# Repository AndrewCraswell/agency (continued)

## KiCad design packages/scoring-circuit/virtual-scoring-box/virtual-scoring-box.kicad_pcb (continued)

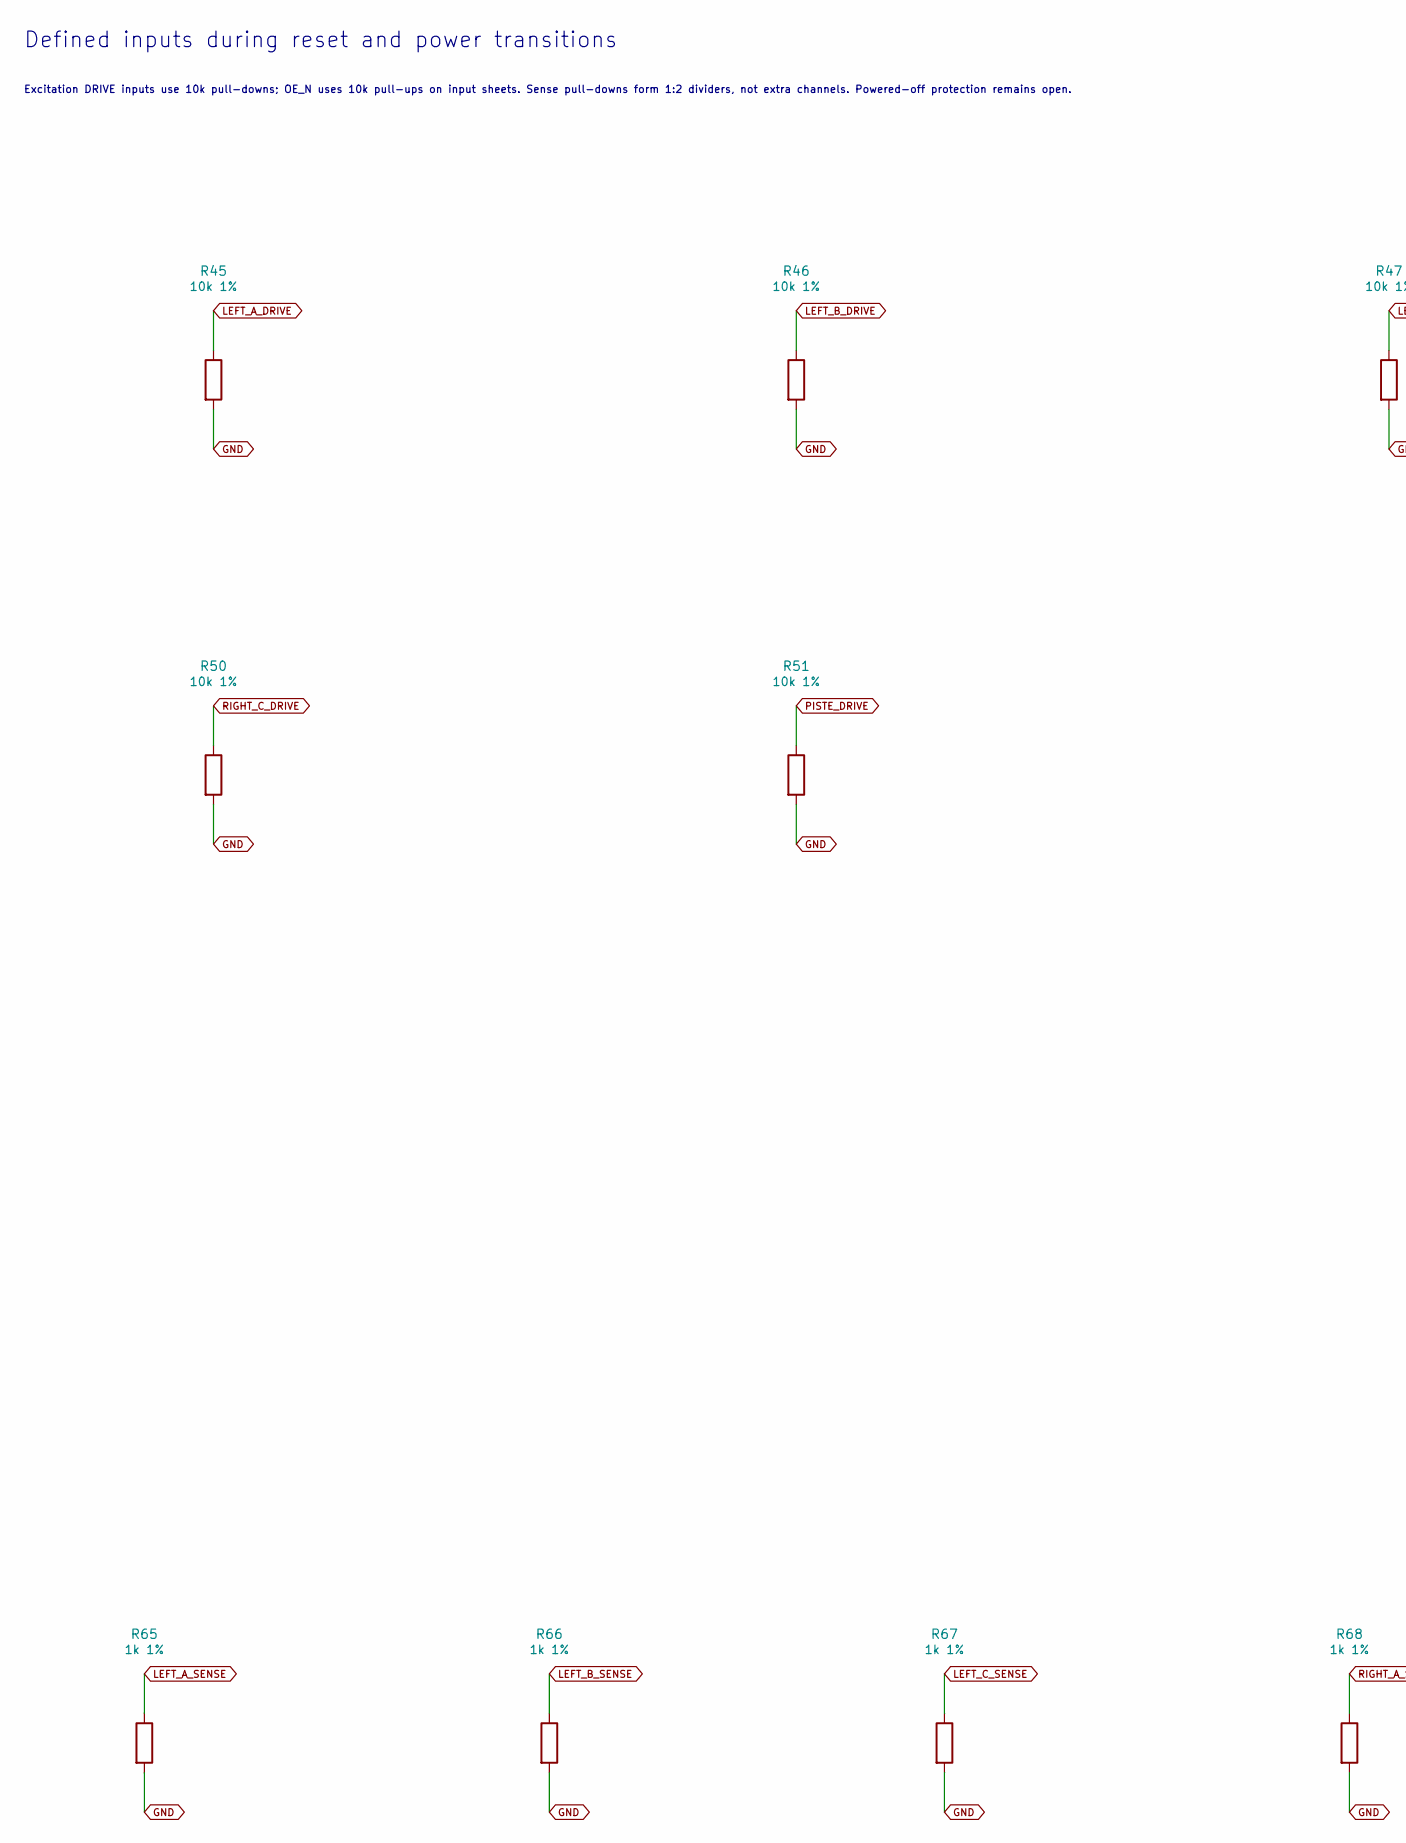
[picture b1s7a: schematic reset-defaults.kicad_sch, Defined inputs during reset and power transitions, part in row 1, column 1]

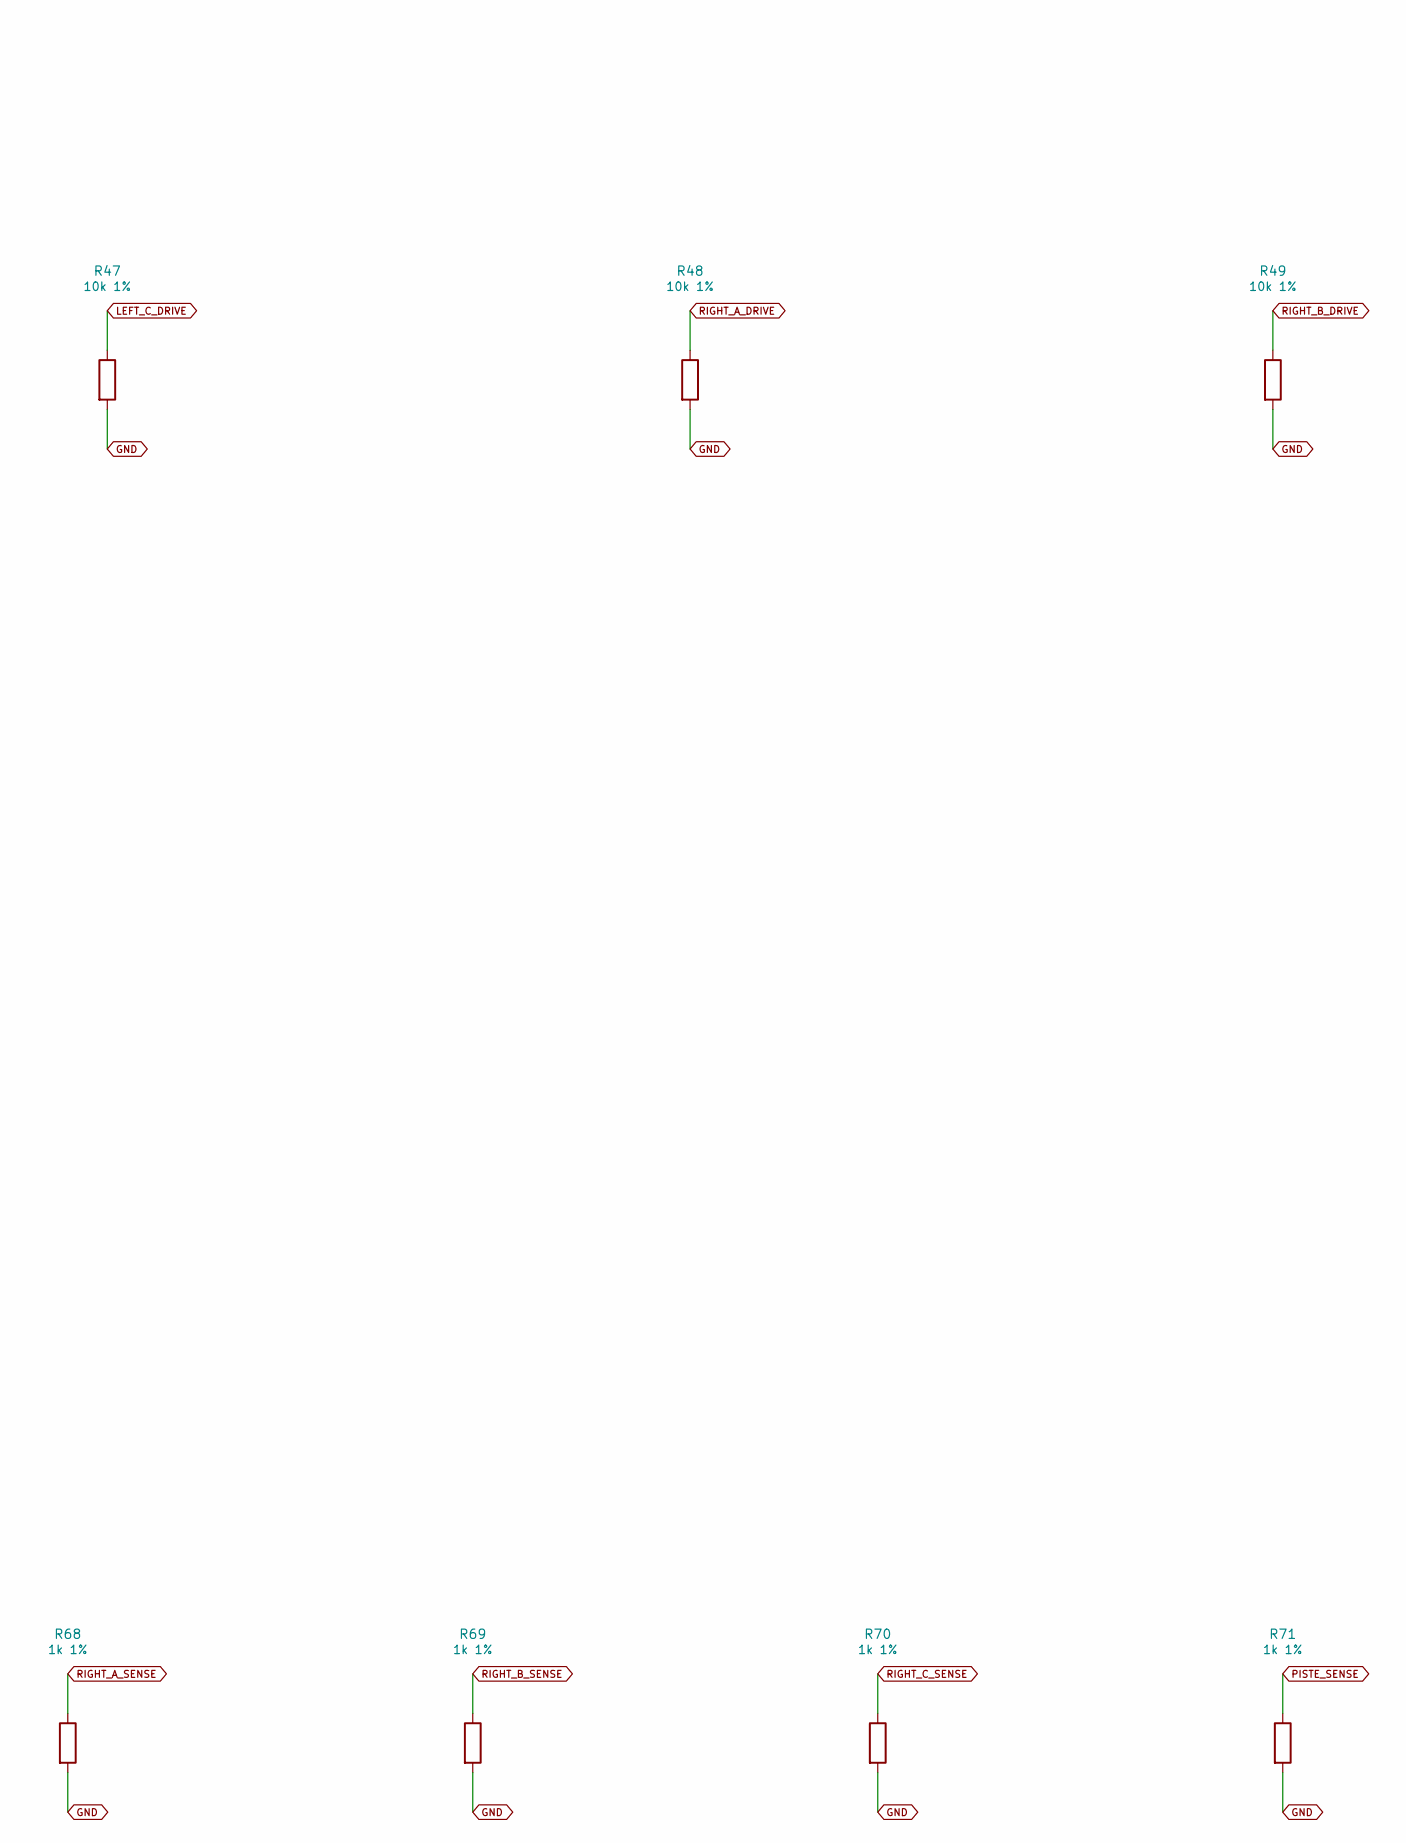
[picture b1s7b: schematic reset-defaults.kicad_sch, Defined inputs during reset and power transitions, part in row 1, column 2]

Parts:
R45, R46, R47, R48, R49, R50, R51: 10k 1%; R_0603_1608Metric; MPN RC0603FR-0710KL
R65, R66, R67, R68, R69, R70, R71: 1k 1%; R_0603_1608Metric; MPN RC0603FR-071KL

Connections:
GND: R45.2, R46.2, R47.2, R48.2, R49.2, R50.2, R51.2, R65.2, R66.2, R67.2, R68.2, R69.2, R70.2, R71.2; also elsewhere on the board
LEFT_A_DRIVE: R45.1; also elsewhere on the board
LEFT_A_SENSE: R65.1; also elsewhere on the board
LEFT_B_DRIVE: R46.1; also elsewhere on the board
LEFT_B_SENSE: R66.1; also elsewhere on the board
LEFT_C_DRIVE: R47.1; also elsewhere on the board
LEFT_C_SENSE: R67.1; also elsewhere on the board
PISTE_DRIVE: R51.1; also elsewhere on the board
PISTE_SENSE: R71.1; also elsewhere on the board
RIGHT_A_DRIVE: R48.1; also elsewhere on the board
RIGHT_A_SENSE: R68.1; also elsewhere on the board
RIGHT_B_DRIVE: R49.1; also elsewhere on the board
RIGHT_B_SENSE: R69.1; also elsewhere on the board
RIGHT_C_DRIVE: R50.1; also elsewhere on the board
RIGHT_C_SENSE: R70.1; also elsewhere on the board

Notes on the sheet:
Defined inputs during reset and power transitions
Excitation DRIVE inputs use 10k pull-downs; OE_N uses 10k pull-ups on input sheets. Sense pull-downs form 1:2 dividers, not extra channels. Powered-off protection remains open.

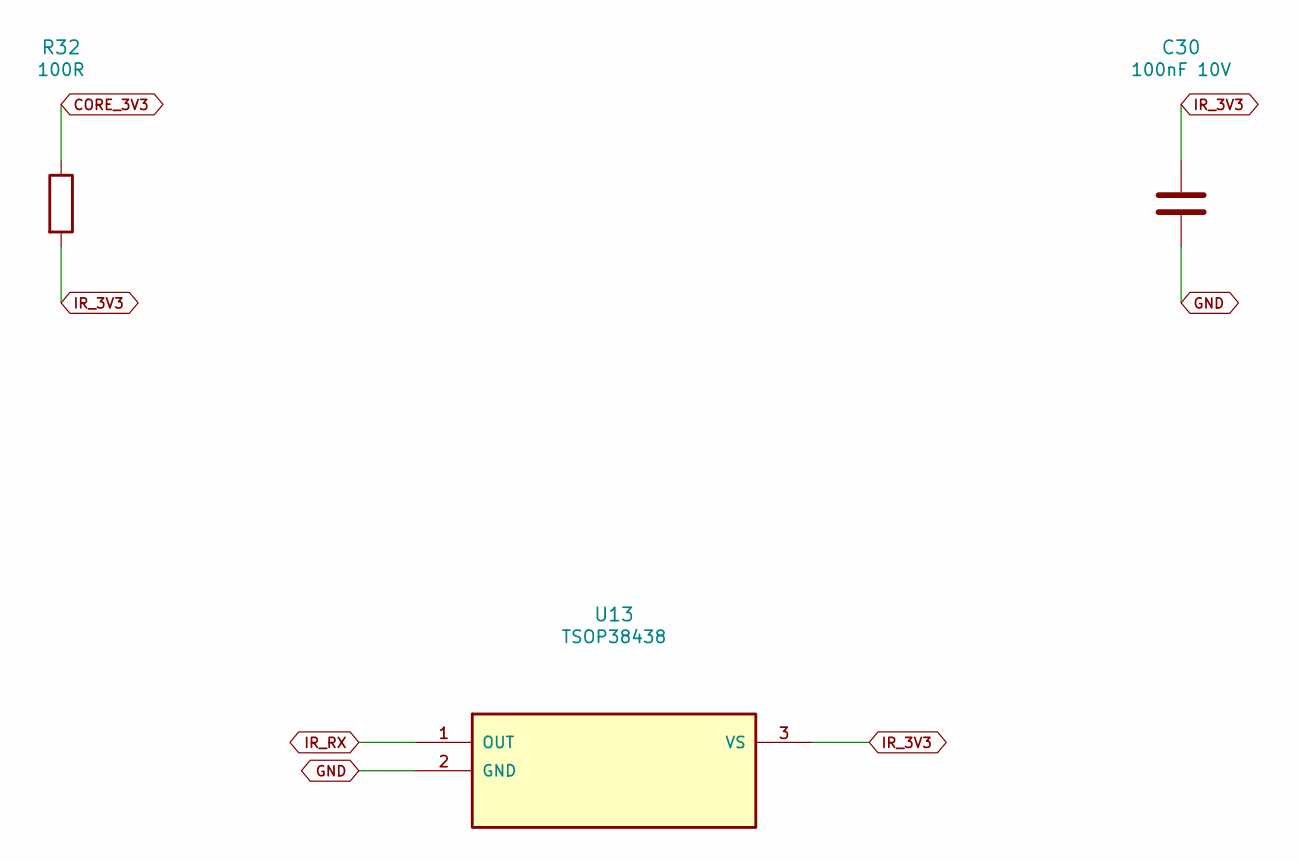
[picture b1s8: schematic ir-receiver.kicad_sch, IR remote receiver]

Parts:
C30: 100nF 10V; C_0603_1608Metric; MPN CC0603KRX7R9BB104
R32: 100R; R_0603_1608Metric; MPN RC0603FR-07100RL
U13: TSOP38438; MPN TSOP38438

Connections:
CORE_3V3: R32.1; also elsewhere on the board
GND: C30.2, U13.2 (GND); also elsewhere on the board
IR_3V3: C30.1, R32.2, U13.3 (VS)
IR_RX: U13.1 (OUT); also elsewhere on the board

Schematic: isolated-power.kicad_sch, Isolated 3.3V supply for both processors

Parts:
C41, C42, C43, C44, C45, C46: 10uF 16V X7R; C_1206_3216Metric; MPN C3216X7R1C106KT000N; JLCPCB C342827
C47: 100nF; C_0603_1608Metric; MPN CC0603KRX7R9BB104
D10, D11: SS14-E3/61T; D_SMA; MPN SS14-E3/61T
L1: 2.2uH; L_Coilcraft_XAL5030-XXX; MPN XAL5030-222MEC
R79: 100k; R_0603_1608Metric; MPN RC0603FR-07100KL
R80: 10k; R_0603_1608Metric; MPN RC0603FR-0710KL
T1: 750315371; MPN 750315371
U21: SN6505BDBVR; SOT-23-6; MPN SN6505BDBVR
U22: TPS62162DSGR; Texas_DSG0008A_WSON-8-1EP_2x2mm_P0.5mm_EP0.9x1.6mm_ThermalV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; MPN TPS62162DSGR

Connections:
CORE_3V3: C45.1, C46.1, L1.2, R80.1, U22.6 (VOS); also elsewhere on the board
CORE_BUCK_SW: L1.1, U22.7 (SW)
GND: C42.2, C43.2, C44.2, C45.2, C46.2, C47.2, R80.2, T1.5, U22.1 (PGND), U22.4 (AGND), U22.5 (FB), U22.9 (PAD); also elsewhere on the board
ISO_UNREG: C42.1, C43.1, C44.1, C47.1, D10.1 (K), D11.1 (K), U22.2 (VIN), U22.3 (EN)
SCORING_POWER_EN: R79.1, U21.5 (EN); also elsewhere on the board
STM_RESET_N: U22.8 (PG); also elsewhere on the board
USB_5V_PROTECTED: C41.1, T1.2, U21.2 (VCC); also elsewhere on the board
USB_GND: C41.2, R79.2, U21.4 (GND), U21.6 (CLK); also elsewhere on the board
XFMR_PRI_A: T1.3, U21.1 (D1)
XFMR_PRI_B: T1.1, U21.3 (D2)
XFMR_SEC_A: D10.2 (A), T1.6
XFMR_SEC_B: D11.2 (A), T1.4

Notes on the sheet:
Isolated supply: protected 5V -> push-pull transformer -> rectifier -> 3.3V / 1A buck
Design target: 0.8A combined 3.3V load, including ESP32 radio peaks, STM32 and acquisition circuits. C45/C46 provide 20uF nominal; 2.2uH / 20uF is within the TPS6216x recommended LC range. T1 is 1:1.1, with primary center tap pin 2 and isolated secondary center tap pin 5. USB_GND must never connect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

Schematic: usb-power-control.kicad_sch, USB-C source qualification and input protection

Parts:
C48, C51, C53, C55, C56, C57, C58: 100nF; C_0603_1608Metric; MPN CC0603KRX7R9BB104
C49, C50, C52: 1uF; C_0603_1608Metric; MPN CC0603KRX7R9BB105; JLCPCB C559769
C54: 10nF; C_0603_1608Metric; MPN CC0603KRX7R9BB103
J7: PRIMARY SWD PADS; Primary_SWD_Pads; MPN PCB contact pads
R81: 23.7k 0.1%; R_0603_1608Metric; MPN RT0603BRD0723K7L; JLCPCB C861245
R82, R84: 10k 0.1%; R_0603_1608Metric; MPN ERA3AEB103V; JLCPCB C190610
R83: 34.8k 0.1%; R_0603_1608Metric; MPN RT0603BRD0734K8L; JLCPCB C861338
R85: 2.74k; R_0603_1608Metric; MPN RC0603FR-072K74L
R86, R87: 4.7k; R_0603_1608Metric; MPN RC0603FR-074K7L
R88, R92: 47k; R_0603_1608Metric; MPN AF0603FR-0747KL; JLCPCB C144107
R89, R90, R91: 100k; R_0603_1608Metric; MPN RC0603FR-07100KL
R93, R94: 1k 1W; R_2512_6332Metric; MPN RC2512FK-071KL
R95: 10k; R_0603_1608Metric; MPN RC0603FR-0710KL
U23: STUSB4500QTR; MPN STUSB4500QTR
U24: STM32C011F6P6; TSSOP-20_4.4x6.5mm_P0.65mm; MPN STM32C011F6P6
U25: TPS259470ARPWR; TPS25947_RPW; MPN TPS259470ARPWR
U26: SN74LVC1G3208DBVR; SOT-23-6; MPN SN74LVC1G3208DBVR
U27: SN74LVC1T45DBVR; SOT-23-6; MPN SN74LVC1T45DBVR

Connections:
FUSE_FAULT_N: R92.2, U24.8 (PA1), U25.4 (FLT_N)
INPUT_DVDT: C54.1, U25.7 (DVDT)
INPUT_ILM: R85.1, U25.9 (ILM)
INPUT_OVLO: R83.2, R84.1, U25.2 (OVLO)
INPUT_UVLO: R81.2, R82.1, U25.1 (EN_UVLO)
PD_1V2: C49.1, U23.21 (VREG_1V2)
PD_2V7: C50.1, U23.23 (VREG_2V7)
PD_ALERT_N: R88.2, U23.19 (ALERT), U24.13 (PA6)
PD_DISCH: R93.2, U23.9 (DISCH)
PD_RESET: R89.1, U23.6 (RESET), U24.7 (PA0)
PD_SCL: R86.2, U23.7 (SCL), U24.20 (PB6)
PD_SDA: R87.2, U23.8 (SDA), U24.1 (PB7)
PD_VBUS_SENSE: R94.2, U23.18 (VBUS_VS_DISCH)
PRIMARY_RESET_N: C58.1, J7.5, R95.2, U24.6 (PF2)
PRIMARY_SWCLK: J7.4, U24.19 (PA14)
PRIMARY_SWDIO: J7.3, U24.18 (PA13)
SCORING_ENABLE_3V3: U26.4, U27.3 (A)
SCORING_POWER_EN: U27.4 (B); also elsewhere on the board
SOURCE_ALLOWED: R90.1, U24.11 (PA4), U26.6
USB_5V_PROTECTED: C57.1, U25.6 (OUT), U27.6 (VCCB); also elsewhere on the board
USB_AWAKE: U24.14 (PA7), U26.1; also elsewhere on the board
USB_CC1: U23.1 (CC1DB), U23.2 (CC1); also elsewhere on the board
USB_CC2: U23.4 (CC2), U23.5 (CC2DB); also elsewhere on the board
USB_GND: C48.2, C49.2, C50.2, C51.2, C52.2, C53.2, C54.2, C55.2, C56.2, C57.2, C58.2, J7.2, R82.2, R84.2, R85.2, R89.2, R90.2, R91.2, U23.10 (GND), U23.12 (ADDR0), U23.13 (ADDR1), U23.22 (VSYS), U23.25 (GND), U24.5 (VSS), U25.8 (GND), U26.2 (GND), U27.2 (GND); also elsewhere on the board
USB_HOST_3V3: C51.1, C52.1, C55.1, C56.1, J7.1, R86.1, R87.1, R88.1, R92.1, R95.1, U24.4 (VDD), U26.5 (VCC), U27.1 (VCCA), U27.5 (DIR); also elsewhere on the board
USB_SUSPEND_EXEMPT: R91.1, U24.12 (PA5), U26.3
USB_VBUS: C48.1, C53.1, R81.1, R83.1, R93.1, R94.1, U23.24 (VDD), U25.5 (IN); also elsewhere on the board

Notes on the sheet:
USB-C 5V input: source qualification, voltage/current protection, hardware suspend cutoff
U23 NVM: one 5V / 1.5A sink PDO; program and read back before shipment. No higher-voltage load mode. SOURCE_ALLOWED requires advertised Type-C >=1.5A OR a valid 5V PD contract >=1.5A; default OFF. USB_SUSPEND_EXEMPT requires current, fresh source evidence, not merely a requested RDO flag. U26: (USB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

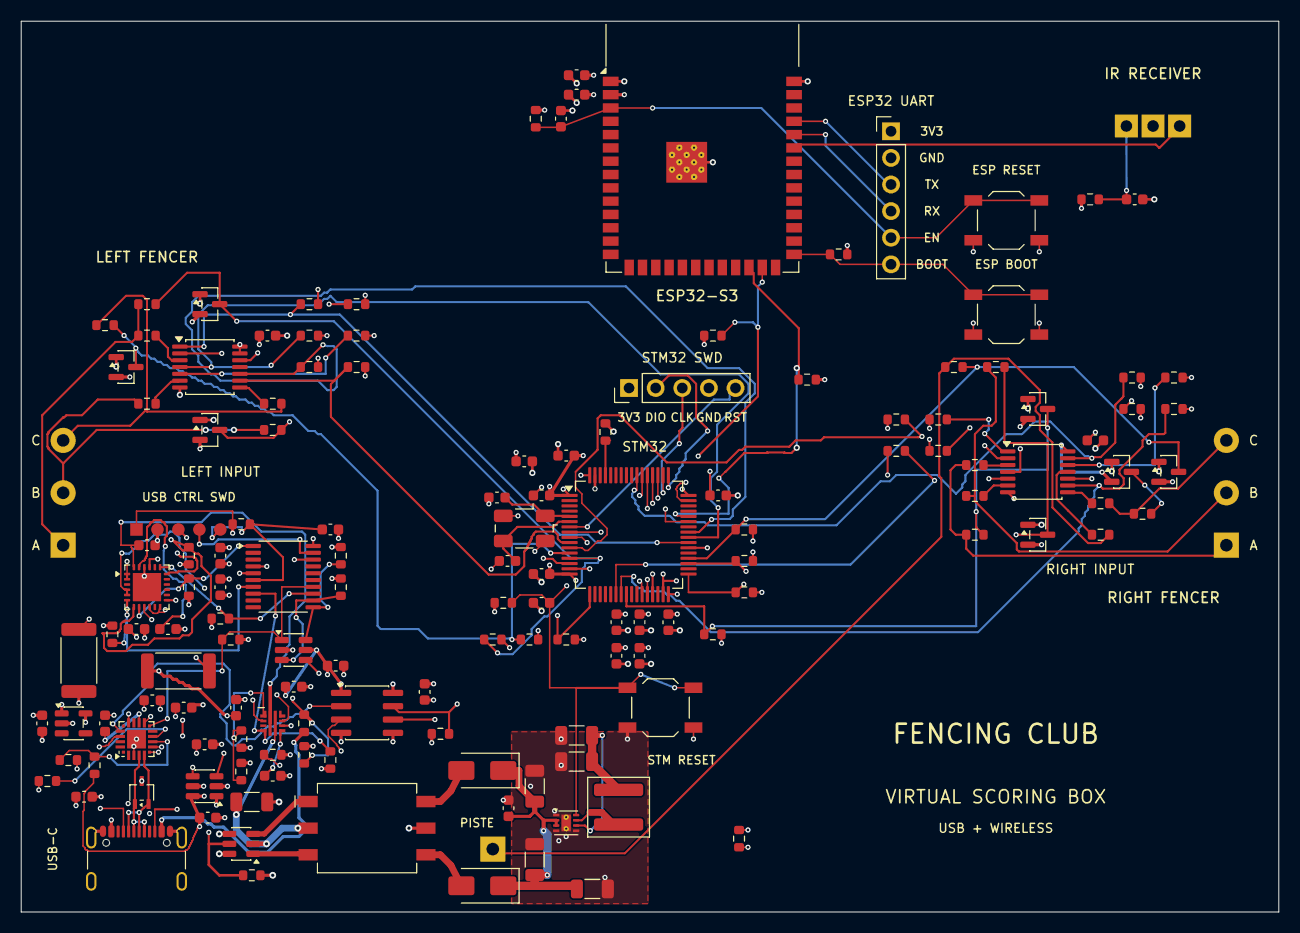
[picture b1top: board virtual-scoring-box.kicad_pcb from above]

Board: 4 copper layers, 120.0 x 85.0 mm, 146 parts (0 on the bottom side), 92 nets.

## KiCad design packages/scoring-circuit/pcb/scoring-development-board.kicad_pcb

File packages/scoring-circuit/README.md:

# Scoring prototype hardware

## Native KiCad designs

- **Active: [virtual scoring box](virtual-scoring-box/README.md).** STM32 scoring, ESP32 wireless/IR, and laptop or
  wall-powered USB-C. The 120 x 85mm board is routed and has a 142-part assembly export. Its README records the current
  JLCPCB draft, component shortages and programming handoff; it is not yet order-ready.
- **Frozen: [combined computer/standalone board](usb-scoring-platform/README.md).** The 165 x 100mm, 223-part design
  includes isolated USB, USB-C PD, Ethernet, IR, HUB75, audio and Favero outputs. Preserve it as a separate reference;
  do not overwrite it with either dedicated product. Its [design review](usb-scoring-platform/design-review.md) retains
  unresolved findings and component checks, not fabrication approval.
- **Active: [standalone HUB75 scoring box](standalone-scoring-box/README.md).** Separate native schematic and routed 165
  x 100mm board with 199 purchased parts. Retains STM32, ESP32, IR, fencer/piste connections, HUB75, Ethernet, Favero
  outputs, audio and power-only USB-C PD; removes the laptop interface and source-mode MCU. The power desk review, U5
  programming procedure and manufacturing exporter are supplied. Four mounting holes and the Ethernet footprint have
  been reviewed; a separate JLCPCB draft is saved. Its README records 34 unresolved sourcing/catalog references, plus
  impedance/programming and physical-test work. It is not order-ready. Firmware logic stays shared, with board-specific
  hardware adapters.

For each native design, use its own README and manufacturing exporter. Keep the latest supplier-upload package and
required programming handoff; older output checkpoints, build caches and scratch routing scripts are disposable. Keep
source, required component models and manufacturer references. Generated output is not a second source of truth.

## Earlier tscircuit carrier

The ESP32 DevKitC/WIZ850io carrier is preserved as the explicitly requested comparison design. Its
[architecture](docs/clean-sheet-board-architecture.md), source and models describe that carrier, not the native board.
Do not mix its BOM, pinout or generated fabrication files with the USB scoring platform.

The following commands operate on that earlier carrier only, not the native KiCad designs.

- `pnpm --filter @repo/scoring-circuit build` generates the circuit JSON, the locally bundled tscircuit RunFrame PCB,
  schematic, and 3D preview, plus the BOM and placement files in `dist/`.
- `pnpm --filter @repo/scoring-circuit pcb:route` regenerates the KiCad project, Gerbers, drill files, BOM, and
  placement files in `pcb/`.
- `pnpm --filter @repo/scoring-circuit test` runs the focused board tests.

The board source sets a red solder mask and white silkscreen for the preview. Gerbers define the mask and silkscreen
geometry, but the fabricator's order form or fabrication notes select the physical pigment; change `solderMaskColor` and
`silkscreenColor` in `src/index.circuit.tsx` when a different finish is chosen.

This is a prototype, not a production or FIE-certified board. Review the KiCad board and fabrication preview before
ordering, then validate the assembled hardware electrically before connecting it to fencing equipment.

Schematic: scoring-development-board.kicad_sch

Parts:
BZ_P0: CMI-9605-0580T
C_APP_REG_BOOT: 100nF
C_APP_REG_IN: 4.7uF
C_APP_REG_IN_HF: 100nF
C_APP_REG_OUT_A: 22uF
C_APP_REG_OUT_B: 22uF
C_APP_REG_OUT_C: 22uF
C_APP_REG_VCC: 1uF
C_DISPLAY_BYPASS: 100nF
C_DISPLAY_DVDT: 2.2nF
C_DISPLAY_IN: 22uF
C_DISPLAY_ITIMER: 2.2nF
C_DISPLAY_OUT: 22uF
C_ESP_3V3_BULK: 47uF
C_ESP_3V3_HF: 100nF
C_ESP_EN_DELAY: 1uF
C_HUB75_BUF_A_BYPASS, C_HUB75_BUF_B_BYPASS: 100nF
C_IR_VS: 100nF
C_NEG_FLY: 1uF
C_NEG_IN: 1uF
C_NEG_OUT: 1uF
C_PHASE_CONTROL_1, C_PHASE_CONTROL_2: 100nF
C_REF_IN: 1uF
C_REF_REG: 10uF
C_REF_REG_HF: 100nF
C_REF_SAR: 10uF
C_SAR: 1nF
C_SAR_AVDD: 1uF
C_SAR_DVDD: 1uF
C_SENSE_MUX: 100nF
C_SENSE_NEG_2, C_SENSE_NEG_3, C_SENSE_NEG_5, C_SENSE_NEG_6, C_SENSE_NEG_7: 100nF
C_SENSE_POS_2, C_SENSE_POS_3, C_SENSE_POS_5, C_SENSE_POS_6, C_SENSE_POS_7: 100nF
C_SINK_MUX: 100nF
C_SOURCE_MUX: 100nF
D_P0_GREEN: WP7113SGD
D_P0_RED: WP7113ID
D_P0_WHITE_LEFT, D_P0_WHITE_RIGHT: WP7113QWC/D
F_DISPLAY: 045106.3MRL
F_MAIN_5V: 0451003.NRL
F_P0_OUTPUTS: 1206L020YR
J_DISPLAY_POWER_PIGTAIL: (no value)
J_HUB75: TST-108-04-G-D-RA
J_PISTE_DIRECT: (no value)
J_POWER_INPUT: OSTVN02A150
J_PRIMARY_OUTPUTS: J_PRIMARY_OUTPUTS
J_USB_C: 10177070-00011LF
J_WEAPON_DIRECT: (no value)
L_APP_REGULATOR: XGL4030-222MEC
Q_DISPLAY_ENABLE: BSS138AKA
R_APP_REG_DISCHARGE: 1kΩ
R_DISPLAY_ENABLE_GATE: 10kΩ
R_DISPLAY_ENABLE_GATE_PD: 100kΩ
R_DISPLAY_ENABLE_PULLUP: 10kΩ
R_DISPLAY_ILM: 698Ω
R_DISPLAY_PG_LOWER: 49.9kΩ
R_DISPLAY_PG_PULLUP: 10kΩ
R_DISPLAY_PG_UPPER: 137kΩ
R_ESP_BOOT_PULLUP: 10kΩ
R_ESP_EN_PULLUP: 10kΩ
R_HUB75_A_PD, R_HUB75_B1_PD, R_HUB75_B2_PD, R_HUB75_B_PD, R_HUB75_CLK_PD, R_HUB75_C_PD, R_HUB75_D_PD, R_HUB75_G1_PD, R_HUB75_G2_PD, R_HUB75_LAT_PD, R_HUB75_OE_PULLUP, R_HUB75_PANEL_OE_PULLUP, R_HUB75_R1_PD, R_HUB75_R2_PD, R_HUB75_UNUSED_B_A6_PD, R_HUB75_UNUSED_B_A7_PD, R_HUB75_UNUSED_B_A8_PD: 10kΩ
R_IR_OUT: 100Ω
R_IR_PULLUP: 10kΩ
R_IR_VS: 100Ω
R_LINE_1, R_LINE_2, R_LINE_3, R_LINE_4, R_LINE_5, R_LINE_6, R_LINE_7: 22Ω
R_P0_BUZZER_INPUT_PD, R_P0_GREEN_INPUT_PD, R_P0_RED_INPUT_PD, R_P0_WHITE_LEFT_INPUT_PD, R_P0_WHITE_RIGHT_INPUT_PD: 100kΩ
R_P0_GREEN_BALLAST, R_P0_RED_BALLAST, R_P0_WHITE_LEFT_BALLAST, R_P0_WHITE_RIGHT_BALLAST: 180Ω
R_PHASE_OE_PULLUP: 100kΩ
R_REF_SAR: 220mΩ
R_SAR: 20Ω
R_SCORING_GROUND_LINK: 0Ω
R_SENSE_EN_PD: 100kΩ
R_SINK_1, R_SINK_2, R_SINK_3, R_SINK_4, R_SINK_5, R_SINK_6, R_SINK_7: 470Ω
R_SINK_EN_PD: 100kΩ
R_SOURCE_1, R_SOURCE_2, R_SOURCE_3, R_SOURCE_4, R_SOURCE_5, R_SOURCE_6, R_SOURCE_7: 470Ω
R_SOURCE_EN_PD: 100kΩ
R_USB_CC1_RD, R_USB_CC2_RD: 5.1kΩ
R_V5_ANALOG_LINK: 0Ω
TP_APP_3V3: TP_APP_3V3
TP_APP_GND: TP_APP_GND
TP_BOOT_N: TP_BOOT_N
TP_EN_RESET: TP_EN_RESET
TP_IR_RX: TP_IR_RX
TP_RECOVERY_APP_3V3: TP_RECOVERY_APP_3V3
TP_UART0_RX: TP_UART0_RX
TP_UART0_TX: TP_UART0_TX
TP_V5: TP_V5
U_APP: ESP32-S3-WROOM-1-N16R2
U_APP_REGULATOR: LMR43620MSC3RPERQ1
U_DISPLAY_BUFFER_A: SN74AHCT245PWR
U_DISPLAY_BUFFER_B: SN74AHCT245PWR
U_DISPLAY_LIMITER: TPS259474ARPWR
U_ESD_1, U_ESD_2: TPD4E05U06DQAR
U_ETHERNET: WIZ850io
U_IR_RX: TSOP38438
U_NEGATIVE_RAIL: TPS60400DBVR
U_P0_OUTPUT_DRIVER: TBD62783AFWG
U_P0_OUTPUT_ESD: TPD6E05U06RVZR
U_PHASE_CONTROL_1, U_PHASE_CONTROL_2: SN74HCS595PWR
U_REF: REF5025AQDRQ1
U_SAR: ADS8881IDGS
U_SENSE_BUFFER_1, U_SENSE_BUFFER_2, U_SENSE_BUFFER_3, U_SENSE_BUFFER_4, U_SENSE_BUFFER_5: ADA4177-1ARZ
U_SENSE_MUX: TMUX1208PWR
U_SINK_MUX: TMUX1208PWR
U_SOURCE_MUX: TMUX1208PWR
U_USB_DATA_PROTECT: TPD2EUSB30DRTR
V5: V5
V5_ANALOG: V5_ANALOG
V5_DISPLAY_LIMITED: V5_DISPLAY_LIMITED
V5_DISPLAY_LOAD: V5_DISPLAY_LOAD
VNEG_ANALOG: VNEG_ANALOG
VREF_2V5: VREF_2V5

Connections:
APP_RESET_N: C_ESP_EN_DELAY.1, R_DISPLAY_ENABLE_GATE.1, R_ESP_EN_PULLUP.1, TP_EN_RESET.1, U_APP.3 (EN_RESET), U_ETHERNET.11 (APP_RESET_N), U_PHASE_CONTROL_1.10 (APP_RESET_N), U_PHASE_CONTROL_2.10 (APP_RESET_N)
APP_SPI_MISO: U_APP.17 (APP_SPI_MISO), U_ETHERNET.12 (APP_SPI_MISO)
APP_SPI_MOSI: U_APP.12 (APP_SPI_MOSI), U_ETHERNET.3 (APP_SPI_MOSI), U_PHASE_CONTROL_1.14 (SERIAL_IN)
APP_SPI_SCK: U_APP.11 (APP_SPI_SCK), U_ETHERNET.4 (APP_SPI_SCK), U_PHASE_CONTROL_1.11 (APP_SPI_SCK), U_PHASE_CONTROL_2.11 (APP_SPI_SCK)
BUZZER: R_P0_BUZZER_INPUT_PD.1, U_APP.19 (BUZZER), U_P0_OUTPUT_DRIVER.5 (IN5)
DISPLAY_ENABLE_N: Q_DISPLAY_ENABLE.3 (DRAIN), R_DISPLAY_ENABLE_PULLUP.1, U_DISPLAY_BUFFER_A.19 (OE_N), U_DISPLAY_BUFFER_B.19 (OE_N)
ETH_CS_N: U_APP.38 (ETH_CS_N), U_ETHERNET.5 (ETH_CS_N)
F_P0_OUTPUTS.V5_PRIMARY_OUTPUTS to U_P0_OUTPUT_DRIVER.V5_PRIMARY_OUTPUTS: F_P0_OUTPUTS.2 (V5_PRIMARY_OUTPUTS), U_P0_OUTPUT_DRIVER.9 (V5_PRIMARY_OUTPUTS)
HUB75_A: R_HUB75_A_PD.1, U_APP.33 (HUB75_A), U_DISPLAY_BUFFER_A.8 (A7_UNUSED)
HUB75_B: R_HUB75_B_PD.1, U_APP.34 (HUB75_B), U_DISPLAY_BUFFER_A.9 (A8_UNUSED)
HUB75_B1: R_HUB75_B1_PD.1, U_APP.23 (HUB75_B1), U_DISPLAY_BUFFER_A.4 (A3)
HUB75_B2: R_HUB75_B2_PD.1, U_APP.32 (HUB75_B2), U_DISPLAY_BUFFER_A.7 (A6_UNUSED)
HUB75_C: R_HUB75_C_PD.1, U_APP.35 (HUB75_C), U_DISPLAY_BUFFER_B.2 (A1)
HUB75_CLK: R_HUB75_CLK_PD.1, U_APP.16 (HUB75_CLK), U_DISPLAY_BUFFER_B.4 (A3)
HUB75_D: R_HUB75_D_PD.1, U_APP.26 (HUB75_D), U_DISPLAY_BUFFER_B.3 (A2)
HUB75_G1: R_HUB75_G1_PD.1, U_APP.22 (HUB75_G1), U_DISPLAY_BUFFER_A.3 (A2)
HUB75_G2: R_HUB75_G2_PD.1, U_APP.31 (HUB75_G2), U_DISPLAY_BUFFER_A.6 (A5)
HUB75_LAT: R_HUB75_LAT_PD.1, U_APP.25 (HUB75_LAT), U_DISPLAY_BUFFER_B.5 (A4)
HUB75_OE_N: R_HUB75_OE_PULLUP.1, U_APP.39 (HUB75_OE_N), U_DISPLAY_BUFFER_B.6 (A5)
HUB75_R1: R_HUB75_R1_PD.1, U_APP.21 (HUB75_R1), U_DISPLAY_BUFFER_A.2 (A1)
HUB75_R2: R_HUB75_R2_PD.1, U_APP.9 (HUB75_R2), U_DISPLAY_BUFFER_A.5 (A4)
IR_RX: R_IR_OUT.2, R_IR_PULLUP.1, TP_IR_RX.1, U_APP.28 (IR_RX)
J_POWER_INPUT.V5_INPUT to F_MAIN_5V.V5_INPUT: F_MAIN_5V.1 (V5_INPUT), J_POWER_INPUT.1 (V5_INPUT)
J_USB_C.CC1 to R_USB_CC1_RD.pin1: J_USB_C.4 (CC1), R_USB_CC1_RD.1
J_USB_C.CC2 to R_USB_CC2_RD.pin1: J_USB_C.9 (CC2), R_USB_CC2_RD.1
LAMP_GREEN: R_P0_GREEN_INPUT_PD.1, U_APP.8 (LAMP_GREEN), U_P0_OUTPUT_DRIVER.2 (IN2)
LAMP_RED: R_P0_RED_INPUT_PD.1, U_APP.7 (LAMP_RED), U_P0_OUTPUT_DRIVER.1 (IN1)
LAMP_WHITE_LEFT: R_P0_WHITE_LEFT_INPUT_PD.1, U_APP.10 (LAMP_WHITE_LEFT), U_P0_OUTPUT_DRIVER.3 (IN3)
LAMP_WHITE_RIGHT: R_P0_WHITE_RIGHT_INPUT_PD.1, U_APP.18 (LAMP_WHITE_RIGHT), U_P0_OUTPUT_DRIVER.4 (IN4)
LEFT_WEAPON_A: J_WEAPON_DIRECT.1 (V5_DISPLAY_BRANCH_1_A), J_WEAPON_DIRECT.7 (APP_GND_BRANCH_2_A), R_LINE_1.1, U_ESD_1.1 (LINE_1)
LEFT_WEAPON_A_PROTECTED: R_LINE_1.2, R_SINK_1.1, R_SOURCE_1.1
LEFT_WEAPON_B: J_WEAPON_DIRECT.2 (V5_DISPLAY_BRANCH_1_B), J_WEAPON_DIRECT.8 (APP_GND_BRANCH_2_B), R_LINE_2.1, U_ESD_1.2 (LINE_2)
LEFT_WEAPON_B_PROTECTED: R_LINE_2.2, R_SINK_2.1, R_SOURCE_2.1, U_SENSE_BUFFER_1.3 (INPUT)
LEFT_WEAPON_C: J_WEAPON_DIRECT.3 (APP_GND_BRANCH_1_A), J_WEAPON_DIRECT.9, R_LINE_3.1, U_ESD_1.4 (LINE_3)
LEFT_WEAPON_C_PROTECTED: R_LINE_3.2, R_SINK_3.1, R_SOURCE_3.1, U_SENSE_BUFFER_2.3 (INPUT)
PISTE: J_PISTE_DIRECT.1 (V5_DISPLAY_BRANCH_1_A), J_PISTE_DIRECT.2 (V5_DISPLAY_BRANCH_1_B), R_LINE_7.1, U_ESD_2.4 (LINE_3)
PISTE_PROTECTED: R_LINE_7.2, R_SINK_7.1, R_SOURCE_7.1, U_SENSE_BUFFER_5.3 (INPUT)
RIGHT_WEAPON_A: J_WEAPON_DIRECT.4 (APP_GND_BRANCH_1_B), J_WEAPON_DIRECT.10, R_LINE_4.1, U_ESD_1.5 (LINE_4)
RIGHT_WEAPON_A_PROTECTED: R_LINE_4.2, R_SINK_4.1, R_SOURCE_4.1
RIGHT_WEAPON_B: J_WEAPON_DIRECT.5 (V5_DISPLAY_BRANCH_2_A), J_WEAPON_DIRECT.11, R_LINE_5.1, U_ESD_2.1 (LINE_1)
RIGHT_WEAPON_B_PROTECTED: R_LINE_5.2, R_SINK_5.1, R_SOURCE_5.1, U_SENSE_BUFFER_3.3 (INPUT)
RIGHT_WEAPON_C: J_WEAPON_DIRECT.6 (V5_DISPLAY_BRANCH_2_B), J_WEAPON_DIRECT.12, R_LINE_6.1, U_ESD_2.2 (LINE_2)
RIGHT_WEAPON_C_PROTECTED: R_LINE_6.2, R_SINK_6.1, R_SOURCE_6.1, U_SENSE_BUFFER_4.3 (INPUT)
R_DISPLAY_ENABLE_GATE.pin2 to Q_DISPLAY_ENABLE.GATE: Q_DISPLAY_ENABLE.1 (GATE), R_DISPLAY_ENABLE_GATE.2, R_DISPLAY_ENABLE_GATE_PD.1
R_DISPLAY_PG_PULLUP.pin2 to U_DISPLAY_LIMITER.PG: R_DISPLAY_PG_PULLUP.2, U_DISPLAY_LIMITER.3 (PG)
R_DISPLAY_PG_UPPER.pin2 to U_DISPLAY_LIMITER.PGTH: R_DISPLAY_PG_LOWER.1, R_DISPLAY_PG_UPPER.2, U_DISPLAY_LIMITER.4 (PGTH)
R_IR_VS.pin2 to U_IR_RX.VS: C_IR_VS.1, R_IR_VS.2, U_IR_RX.3 (VS)
R_P0_GREEN_BALLAST.pin2 to D_P0_GREEN.ANODE: D_P0_GREEN.1 (ANODE), R_P0_GREEN_BALLAST.2
R_P0_RED_BALLAST.pin2 to D_P0_RED.ANODE: D_P0_RED.1 (ANODE), R_P0_RED_BALLAST.2
R_P0_WHITE_LEFT_BALLAST.pin2 to D_P0_WHITE_LEFT.ANODE: D_P0_WHITE_LEFT.1 (ANODE), R_P0_WHITE_LEFT_BALLAST.2
R_P0_WHITE_RIGHT_BALLAST.pin2 to D_P0_WHITE_RIGHT.ANODE: D_P0_WHITE_RIGHT.1 (ANODE), R_P0_WHITE_RIGHT_BALLAST.2
R_REF_SAR.pin2 to U_SAR.REF_2V5: C_REF_SAR.1, R_REF_SAR.2, U_SAR.1 (REF_2V5)
R_SAR.pin2 to U_SAR.AINP: C_SAR.1, R_SAR.2, U_SAR.3 (AINP)
R_SINK_1.pin2 to U_SINK_MUX.S1: R_SINK_1.2, U_SINK_MUX.4 (S1)
R_SINK_2.pin2 to U_SINK_MUX.S2: R_SINK_2.2, U_SINK_MUX.5 (S2)
R_SINK_3.pin2 to U_SINK_MUX.S3: R_SINK_3.2, U_SINK_MUX.6 (S3)
R_SINK_4.pin2 to U_SINK_MUX.S4: R_SINK_4.2, U_SINK_MUX.7 (S4)
R_SINK_5.pin2 to U_SINK_MUX.S5: R_SINK_5.2, U_SINK_MUX.12 (S5)
R_SINK_6.pin2 to U_SINK_MUX.S6: R_SINK_6.2, U_SINK_MUX.11 (S6)
R_SINK_7.pin2 to U_SINK_MUX.S7: R_SINK_7.2, U_SINK_MUX.10 (S7)
R_SOURCE_1.pin2 to U_SOURCE_MUX.S1: R_SOURCE_1.2, U_SOURCE_MUX.4 (S1)
R_SOURCE_2.pin2 to U_SOURCE_MUX.S2: R_SOURCE_2.2, U_SOURCE_MUX.5 (S2)
R_SOURCE_3.pin2 to U_SOURCE_MUX.S3: R_SOURCE_3.2, U_SOURCE_MUX.6 (S3)
R_SOURCE_4.pin2 to U_SOURCE_MUX.S4: R_SOURCE_4.2, U_SOURCE_MUX.7 (S4)
R_SOURCE_5.pin2 to U_SOURCE_MUX.S5: R_SOURCE_5.2, U_SOURCE_MUX.12 (S5)
R_SOURCE_6.pin2 to U_SOURCE_MUX.S6: R_SOURCE_6.2, U_SOURCE_MUX.11 (S6)
R_SOURCE_7.pin2 to U_SOURCE_MUX.S7: R_SOURCE_7.2, U_SOURCE_MUX.10 (S7)
SAR_CONVST: U_APP.6 (SAR_CONVST), U_SAR.6 (SAR_CONVST)
SAR_DOUT: U_APP.5 (SAR_DOUT), U_SAR.7 (SAR_DOUT)
SAR_SCLK: U_APP.4 (SAR_SCLK), U_SAR.8 (SAR_SCLK)
SENSE_A0: U_PHASE_CONTROL_2.15 (Q0), U_SENSE_MUX.1 (A0)
SENSE_A1: U_PHASE_CONTROL_2.1 (Q1), U_SENSE_MUX.16 (A1)
SENSE_A2: U_PHASE_CONTROL_2.2 (Q2), U_SENSE_MUX.15 (A2)
SENSE_EN: R_SENSE_EN_PD.1, U_PHASE_CONTROL_2.3 (Q3), U_SENSE_MUX.2 (EN)
SINK_A0: U_PHASE_CONTROL_1.4 (Q4), U_SINK_MUX.1 (A0)
SINK_A1: U_PHASE_CONTROL_1.5 (Q5), U_SINK_MUX.16 (A1)
SINK_A2: U_PHASE_CONTROL_1.6 (Q6), U_SINK_MUX.15 (A2)
SINK_EN: R_SINK_EN_PD.1, U_PHASE_CONTROL_1.7 (Q7), U_SINK_MUX.2 (EN)
SOURCE_A0: U_PHASE_CONTROL_1.15 (Q0), U_SOURCE_MUX.1 (A0)
SOURCE_A1: U_PHASE_CONTROL_1.1 (Q1), U_SOURCE_MUX.16 (A1)
SOURCE_A2: U_PHASE_CONTROL_1.2 (Q2), U_SOURCE_MUX.15 (A2)
SOURCE_EN: R_SOURCE_EN_PD.1, U_PHASE_CONTROL_1.3 (Q3), U_SOURCE_MUX.2 (EN)
SOURCE_LATCH: U_APP.24 (SOURCE_LATCH), U_PHASE_CONTROL_1.12 (SOURCE_LATCH), U_PHASE_CONTROL_2.12 (SOURCE_LATCH)
SOURCE_OE_N: R_PHASE_OE_PULLUP.1, U_APP.29 (SOURCE_OE_N), U_PHASE_CONTROL_1.13 (SOURCE_OE_N), U_PHASE_CONTROL_2.13 (SOURCE_OE_N)
USB_DN: J_USB_C.5 (Dn2), J_USB_C.7 (Dn1), U_APP.13 (USB_DN), U_USB_DATA_PROTECT.2 (D-)
U_APP.BOOT_N to R_ESP_BOOT_PULLUP.pin1: R_ESP_BOOT_PULLUP.1, TP_BOOT_N.1, U_APP.27 (BOOT_N)
U_APP.UART0_RX to TP_UART0_RX.pin1: TP_UART0_RX.1, U_APP.36 (UART0_RX)
U_APP.UART0_TX to TP_UART0_TX.pin1: TP_UART0_TX.1, U_APP.37 (UART0_TX)
U_APP_REGULATOR.MODE_SYNC to U_APP_REGULATOR.VCC: C_APP_REG_VCC.1, U_APP_REGULATOR.1 (MODE_SYNC), U_APP_REGULATOR.7 (VCC)
U_DISPLAY_BUFFER_A.B1 to J_HUB75.R1: J_HUB75.1 (R1), U_DISPLAY_BUFFER_A.18 (B1)
U_DISPLAY_BUFFER_A.B2 to J_HUB75.G1: J_HUB75.2 (G1), U_DISPLAY_BUFFER_A.17 (B2)
U_DISPLAY_BUFFER_A.B3 to J_HUB75.B1: J_HUB75.3 (B1), U_DISPLAY_BUFFER_A.16 (B3)
U_DISPLAY_BUFFER_A.B4 to J_HUB75.R2: J_HUB75.5 (R2), U_DISPLAY_BUFFER_A.15 (B4)
U_DISPLAY_BUFFER_A.B5 to J_HUB75.G2: J_HUB75.6 (G2), U_DISPLAY_BUFFER_A.14 (B5)
U_DISPLAY_BUFFER_A.B6 to J_HUB75.B2: J_HUB75.7 (B2), U_DISPLAY_BUFFER_A.13 (B6_NC)
U_DISPLAY_BUFFER_A.B7 to J_HUB75.A: J_HUB75.9 (A), U_DISPLAY_BUFFER_A.12 (B7_NC)
U_DISPLAY_BUFFER_A.B8 to J_HUB75.B: J_HUB75.10 (B), U_DISPLAY_BUFFER_A.11 (B8_NC)
U_DISPLAY_BUFFER_B.A6_UNUSED to R_HUB75_UNUSED_B_A6_PD.pin1: R_HUB75_UNUSED_B_A6_PD.1, U_DISPLAY_BUFFER_B.7 (A6_UNUSED)
U_DISPLAY_BUFFER_B.A7_UNUSED to R_HUB75_UNUSED_B_A7_PD.pin1: R_HUB75_UNUSED_B_A7_PD.1, U_DISPLAY_BUFFER_B.8 (A7_UNUSED)
U_DISPLAY_BUFFER_B.A8_UNUSED to R_HUB75_UNUSED_B_A8_PD.pin1: R_HUB75_UNUSED_B_A8_PD.1, U_DISPLAY_BUFFER_B.9 (A8_UNUSED)
U_DISPLAY_BUFFER_B.B1 to J_HUB75.C: J_HUB75.11 (C), U_DISPLAY_BUFFER_B.18 (B1)
U_DISPLAY_BUFFER_B.B2 to J_HUB75.D: J_HUB75.12 (D), U_DISPLAY_BUFFER_B.17 (B2)
U_DISPLAY_BUFFER_B.B3 to J_HUB75.CLK: J_HUB75.13 (CLK), U_DISPLAY_BUFFER_B.16 (B3)
U_DISPLAY_BUFFER_B.B4 to J_HUB75.LAT: J_HUB75.14 (LAT), U_DISPLAY_BUFFER_B.15 (B4)
U_DISPLAY_BUFFER_B.B5 to J_HUB75.OE: J_HUB75.15 (OE), R_HUB75_PANEL_OE_PULLUP.1, U_DISPLAY_BUFFER_B.14 (B5)
U_DISPLAY_LIMITER.DVDT to C_DISPLAY_DVDT.pin1: C_DISPLAY_DVDT.1, U_DISPLAY_LIMITER.7 (DVDT)
U_DISPLAY_LIMITER.ILM to R_DISPLAY_ILM.pin1: R_DISPLAY_ILM.1, U_DISPLAY_LIMITER.9 (ILM)
U_DISPLAY_LIMITER.ITIMER to C_DISPLAY_ITIMER.pin1: C_DISPLAY_ITIMER.1, U_DISPLAY_LIMITER.10 (ITIMER)
U_IR_RX.OUT to R_IR_OUT.pin1: R_IR_OUT.1, U_IR_RX.1 (OUT)
U_NEGATIVE_RAIL.CFLY_NEG to C_NEG_FLY.pin1: C_NEG_FLY.1, U_NEGATIVE_RAIL.3 (CFLY_NEG)
U_NEGATIVE_RAIL.CFLY_POS to C_NEG_FLY.pin2: C_NEG_FLY.2, U_NEGATIVE_RAIL.5 (CFLY_POS)
U_P0_OUTPUT_DRIVER.OUT1 to U_P0_OUTPUT_ESD.CH1_RED: J_PRIMARY_OUTPUTS.1 (CIRCUIT_1_RED), R_P0_RED_BALLAST.1, U_P0_OUTPUT_DRIVER.18 (OUT1), U_P0_OUTPUT_ESD.14 (CH1_RED)
U_P0_OUTPUT_DRIVER.OUT2 to U_P0_OUTPUT_ESD.CH2_GREEN: J_PRIMARY_OUTPUTS.2 (CIRCUIT_2_GREEN), R_P0_GREEN_BALLAST.1, U_P0_OUTPUT_DRIVER.17 (OUT2), U_P0_OUTPUT_ESD.13 (CH2_GREEN)
U_P0_OUTPUT_DRIVER.OUT3 to U_P0_OUTPUT_ESD.CH3_WHITE_LEFT: J_PRIMARY_OUTPUTS.3 (CIRCUIT_3_WHITE_LEFT), R_P0_WHITE_LEFT_BALLAST.1, U_P0_OUTPUT_DRIVER.16 (OUT3), U_P0_OUTPUT_ESD.12 (CH3_WHITE_LEFT)
U_P0_OUTPUT_DRIVER.OUT4 to U_P0_OUTPUT_ESD.CH4_WHITE_RIGHT: J_PRIMARY_OUTPUTS.4 (CIRCUIT_4_WHITE_RIGHT), R_P0_WHITE_RIGHT_BALLAST.1, U_P0_OUTPUT_DRIVER.15 (OUT4), U_P0_OUTPUT_ESD.11 (CH4_WHITE_RIGHT)
U_P0_OUTPUT_DRIVER.OUT5 to U_P0_OUTPUT_ESD.CH5_BUZZER: BZ_P0.1 (POSITIVE), J_PRIMARY_OUTPUTS.5 (CIRCUIT_5_BUZZER), U_P0_OUTPUT_DRIVER.14 (OUT5), U_P0_OUTPUT_ESD.9 (CH5_BUZZER)
U_PHASE_CONTROL_1.SERIAL_OUT to U_PHASE_CONTROL_2.SERIAL_IN: U_PHASE_CONTROL_1.9 (SERIAL_OUT), U_PHASE_CONTROL_2.14 (SERIAL_IN)
U_SENSE_BUFFER_1.OUTPUT to U_SENSE_BUFFER_1.INVERTING: U_SENSE_BUFFER_1.2 (INVERTING), U_SENSE_BUFFER_1.6 (OUTPUT), U_SENSE_MUX.5 (S2)
U_SENSE_BUFFER_2.OUTPUT to U_SENSE_BUFFER_2.INVERTING: U_SENSE_BUFFER_2.2 (INVERTING), U_SENSE_BUFFER_2.6 (OUTPUT), U_SENSE_MUX.6 (S3)
U_SENSE_BUFFER_3.OUTPUT to U_SENSE_BUFFER_3.INVERTING: U_SENSE_BUFFER_3.2 (INVERTING), U_SENSE_BUFFER_3.6 (OUTPUT), U_SENSE_MUX.12 (S5)
U_SENSE_BUFFER_4.OUTPUT to U_SENSE_BUFFER_4.INVERTING: U_SENSE_BUFFER_4.2 (INVERTING), U_SENSE_BUFFER_4.6 (OUTPUT), U_SENSE_MUX.11 (S6)
U_SENSE_BUFFER_5.OUTPUT to U_SENSE_BUFFER_5.INVERTING: U_SENSE_BUFFER_5.2 (INVERTING), U_SENSE_BUFFER_5.6 (OUTPUT), U_SENSE_MUX.10 (S7)
U_SENSE_MUX.D to R_SAR.pin1: R_SAR.1, U_SENSE_MUX.8 (D)
V5: C_APP_REG_IN.1, C_APP_REG_IN_HF.1, C_DISPLAY_BYPASS.1, C_DISPLAY_IN.1, F_MAIN_5V.2 (V5_FUSED), F_P0_OUTPUTS.1 (V5), R_V5_ANALOG_LINK.1, TP_V5.1, U_APP_REGULATOR.3 (EN_UVLO), U_APP_REGULATOR.4 (VIN), U_DISPLAY_LIMITER.1 (EN_UVLO), U_DISPLAY_LIMITER.5 (IN), V5.1
V5_ANALOG: C_NEG_IN.1, C_REF_IN.1, C_SENSE_POS_2.1, C_SENSE_POS_3.1, C_SENSE_POS_5.1, C_SENSE_POS_6.1, C_SENSE_POS_7.1, R_V5_ANALOG_LINK.2, U_NEGATIVE_RAIL.2 (V5_ANALOG), U_REF.2 (V5_ANALOG), U_SENSE_BUFFER_1.7 (V5_ANALOG), U_SENSE_BUFFER_2.7 (V5_ANALOG), U_SENSE_BUFFER_3.7 (V5_ANALOG), U_SENSE_BUFFER_4.7 (V5_ANALOG), U_SENSE_BUFFER_5.7 (V5_ANALOG), V5_ANALOG.1
V5_DISPLAY_LIMITED: C_DISPLAY_OUT.1, C_HUB75_BUF_A_BYPASS.1, C_HUB75_BUF_B_BYPASS.1, F_DISPLAY.1 (FUSED_IN), R_DISPLAY_ENABLE_PULLUP.2, R_DISPLAY_PG_UPPER.1, R_HUB75_PANEL_OE_PULLUP.2, U_DISPLAY_BUFFER_A.1 (DIR), U_DISPLAY_BUFFER_A.20 (V5_DISPLAY_LIMITED), U_DISPLAY_BUFFER_B.1 (DIR), U_DISPLAY_BUFFER_B.20 (V5_DISPLAY_LIMITED), U_DISPLAY_LIMITER.6 (OUT), V5_DISPLAY_LIMITED.1
V5_DISPLAY_LOAD: F_DISPLAY.2 (FUSED_OUT), J_DISPLAY_POWER_PIGTAIL.1 (V5_DISPLAY_BRANCH_1_A), J_DISPLAY_POWER_PIGTAIL.2 (V5_DISPLAY_BRANCH_1_B), J_DISPLAY_POWER_PIGTAIL.5 (V5_DISPLAY_BRANCH_2_A), J_DISPLAY_POWER_PIGTAIL.6 (V5_DISPLAY_BRANCH_2_B), V5_DISPLAY_LOAD.1
VNEG_ANALOG: C_NEG_OUT.1, C_SENSE_NEG_2.1, C_SENSE_NEG_3.1, C_SENSE_NEG_5.1, C_SENSE_NEG_6.1, C_SENSE_NEG_7.1, U_NEGATIVE_RAIL.1 (VNEG_ANALOG), U_SENSE_BUFFER_1.4 (VNEG_ANALOG), U_SENSE_BUFFER_2.4 (VNEG_ANALOG), U_SENSE_BUFFER_3.4 (VNEG_ANALOG), U_SENSE_BUFFER_4.4 (VNEG_ANALOG), U_SENSE_BUFFER_5.4 (VNEG_ANALOG), VNEG_ANALOG.1
VREF_2V5: C_REF_REG.2 (1), C_REF_REG_HF.1, R_REF_SAR.1, U_REF.6 (VREF_2V5), U_SOURCE_MUX.8 (D), VREF_2V5.1

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
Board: 4 copper layers, 164 parts (0 on the bottom side), 135 nets, no tracks yet.
